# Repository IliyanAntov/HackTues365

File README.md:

# HackTues365 Project
Defuse the bomb.

## Game Rules And Tutorial

Work with a partner to defuse the bomb.
One of the two players should only look at the instructions while the other one is defusing the bomb.
Adhere to the time limit otherwise the bomb explodes.

Have fun!

## How do I play?

Connect your **Arduino** board the PC and then start the Generator app.
Click **Generate** and wait for the instructions to upload.
You can then disconnect the board and start playing the game.

## Used Technologies

All of the game logic relies on the **Arduino** to run on.
The random values for each game are generated by a **.NET Windows Forms Application**.
Both processes are connected via a serial connection based on the **System.IO.Ports** library included in **.NET**.

## Dependecies

The schematic is based on an open source Arduino Mega 2560 design by [Yoyodyne Monkey Works, Inc.](https://github.com/YoyodyneMonkeyWorks)

Repository [link](https://github.com/YoyodyneMonkeyWorks/KiCad/tree/master/Arduino_MEGA_2560-Rev3)

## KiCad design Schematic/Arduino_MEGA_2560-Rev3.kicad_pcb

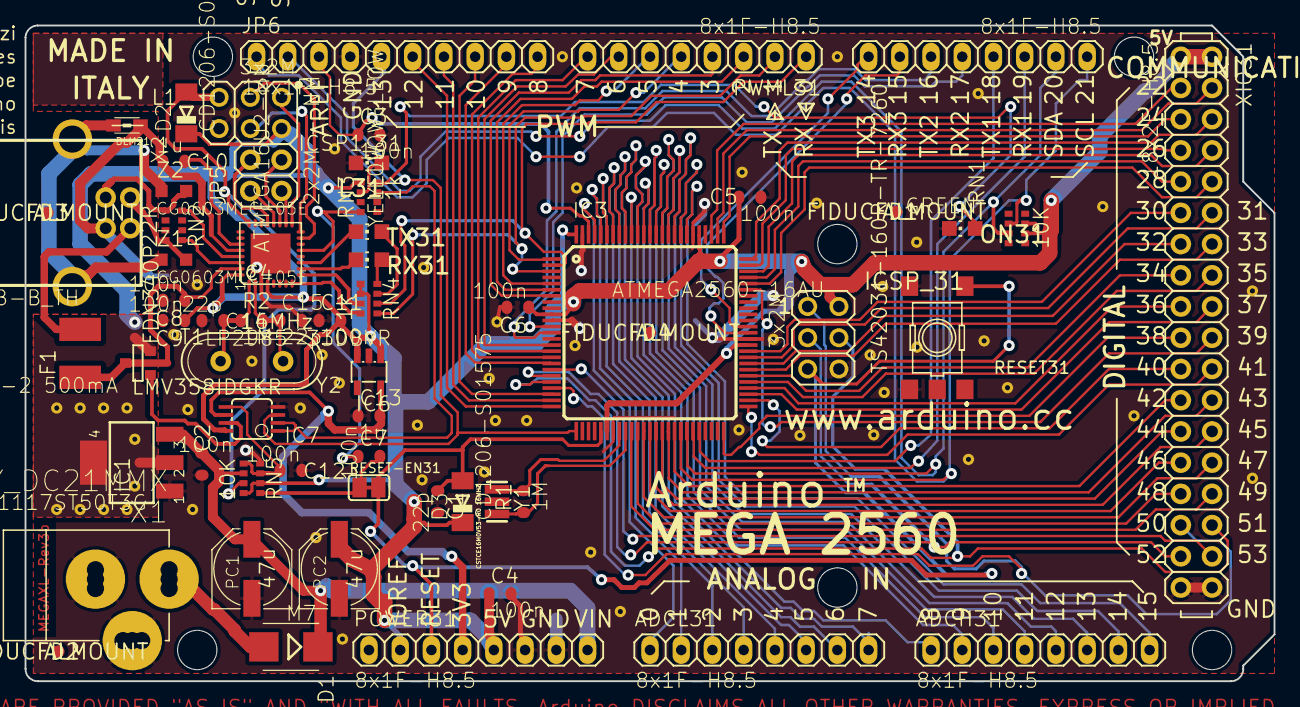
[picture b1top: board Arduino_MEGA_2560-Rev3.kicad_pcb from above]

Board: 2 copper layers, 101.6 x 53.3 mm, 69 parts (0 on the bottom side), 110 nets.

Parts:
@HOLE0, @HOLE1, @HOLE2, @HOLE3, @HOLE4, @HOLE5: (no value)
ADCH31: 8x1F-H8.5; 1X08
ADCL31: 8x1F-H8.5; 1X08
C1, C14, C15: 22p; C0603-ROUND
C2, C3, C4, C5, C6, C7, C8, C9, C11, C12: 100n; C0603-ROUND
C10, C13: 1u; C0603-ROUND
COMMUNICATION31: 8x1F-H8.5; 1X08
D1: M7; SMB
D2, D3: CD1206-S01575; MINIMELF
F1: MF-MSMF050-2 500mA; L1812
FD1, FD2, FD3, FD4: FIDUCIALMOUNT; FIDUCIA-MOUNT
GROUND31: SJ
IC1: NCP1117ST50T3G; SOT223
IC3: ATMEGA2560-16AU; TQFP100
IC4: ATMEGA16U2-MU; MLF32
IC6: LP2985-33DBVR; SOT23-DBV
IC7: LMV358IDGKR; MSOP08
ICSP1_31: 3x2M; 2X03
ICSP_31: 3x2M; 2X03
JP5: 2x2M - NM; 2X02
JP6: 10x1F-H8.5; 1X10
L1: BLM21; 0805
L31: YELLOW; CHIP-LED0805
ON31: GREEN; CHIP-LED0805
PC1, PC2: 47u; PANASONIC_D
POWER31: 8x1F-H8.5; 1X08
PWML31: 8x1F-H8.5; 1X08
R1, R2: 1M; R0603-ROUND
RESET31: TS42031-160R-TR-7260; TS42
RESET-EN31: SJ
RN1, RN5: 10K; CAT16
RN2: 22R; CAY16
RN3, RN4: 1k; CAY16
RX31: YELLOW; CHIP-LED0805
T1: FDN340P; SOT-23
TX31: YELLOW; CHIP-LED0805
U$1: DISCLAIMER
X1: POWERSUPPLY_DC21MMX; POWERSUPPLY_DC-21MM
X2: USB-B_TH; PN61729
XIO31: 18x2F-H8.5; 2X18
Y1: CSTCE16M0V53-R0 16MHZ; RESONATOR
Y2: 16MHz; QS
Z1, Z2: CG0603MLC-05E; CT%2fCN0603

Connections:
+3V3: C13.2, IC6.5, IC7.6, POWER31.4
+5V: C4.1, C5.1, C6.1, C9.1, C11.2, D2.C, D3.C, IC1.2, IC1.4, IC3.10, IC3.31, IC3.61, IC3.80, IC3.100, IC4.4, IC4.32, IC6.1, IC6.3, IC7.8, ICSP1_31.2, ICSP_31.2, PC2.+, POWER31.2, POWER31.5, RN1.6, RN1.7, RN3.1, RN4.5, RN4.6, RN5.2, RN5.8, T1.2, XIO31.1, XIO31.2
/8PB4: IC4.18, JP5.1
/8PB5: IC4.19, JP5.3
/8PB6: IC4.20, JP5.2
/8PB7: IC4.21, JP5.4
/ADC0: ADCL31.1, IC3.97
/ADC1: ADCL31.2, IC3.96
/ADC2: ADCL31.3, IC3.95
/ADC3: ADCL31.4, IC3.94
/ADC4: ADCL31.5, IC3.93
/ADC5: ADCL31.6, IC3.92
/ADC6: ADCL31.7, IC3.91
/ADC7: ADCL31.8, IC3.90
/ADC8: ADCH31.1, IC3.89
/ADC9: ADCH31.2, IC3.88
/ADC10: ADCH31.3, IC3.87
/ADC11: ADCH31.4, IC3.86
/ADC12: ADCH31.5, IC3.85
/ADC13: ADCH31.6, IC3.84
/ADC14: ADCH31.7, IC3.83
/ADC15: ADCH31.8, IC3.82
/AREF: C3.1, IC3.98, JP6.3
/CMP: C12.2, IC7.5, RN5.3, RN5.5
/D+: RN2.5, X2.3, Z2.2
/D-: RN2.8, X2.2, Z1.2
/DTR: C7.1, IC4.13, RN3.4
/GATE_CMD: IC7.7, T1.3
/L13: IC7.1, IC7.2, RN3.7
/M8RXD: IC4.9, RN4.7
/M8TXD: IC4.8, RN4.8
/MISO2: IC4.17, ICSP1_31.1
/MOSI2: IC4.16, ICSP1_31.4
/N$2: L31.A, RN3.2
/N$3: ON31.A, RN3.8
/N$54: RN4.4, RX31.A
/N$55: RN4.3, TX31.A
/PA0: IC3.78, XIO31.3
/PA1: IC3.77, XIO31.4
/PA2: IC3.76, XIO31.5
/PA3: IC3.75, XIO31.6
/PA4: IC3.74, XIO31.7
/PA5: IC3.73, XIO31.8
/PA6: IC3.72, XIO31.9
/PA7: IC3.71, XIO31.10
/PB0: IC3.19, XIO31.34
/PB1: IC3.20, ICSP_31.3, XIO31.33
/PB2: IC3.21, ICSP_31.4, XIO31.32
/PB3: IC3.22, ICSP_31.1, XIO31.31
/PB4: IC3.23, JP6.8
/PB5: IC3.24, JP6.7
/PB6: IC3.25, JP6.6
/PB7: IC3.26, IC7.3, JP6.5
/PC0: IC3.53, XIO31.18
/PC1: IC3.54, XIO31.17
/PC2: IC3.55, XIO31.16
/PC3: IC3.56, XIO31.15
/PC4: IC3.57, XIO31.14
/PC5: IC3.58, XIO31.13
/PC6: IC3.59, XIO31.12
/PC7: IC3.60, XIO31.11
/PD7: IC3.50, XIO31.19
/PE0: IC3.2, PWML31.1, RN4.2
/PE1: IC3.3, PWML31.2, RN4.1
/PE3: IC3.5, PWML31.6
/PE4: IC3.6, PWML31.3
/PE5: IC3.7, PWML31.4
/PG0: IC3.51, XIO31.22
/PG1: IC3.52, XIO31.21
/PG2: IC3.70, XIO31.20
/PG5: IC3.1, PWML31.5
/PH3: IC3.15, PWML31.7
/PH4: IC3.16, PWML31.8
/PH5: IC3.17, JP6.10
/PH6: IC3.18, JP6.9
/PL0: IC3.35, XIO31.30
/PL1: IC3.36, XIO31.29
/PL2: IC3.37, XIO31.28
/PL3: IC3.38, XIO31.27
/PL4: IC3.39, XIO31.26
/PL5: IC3.40, XIO31.25
/PL6: IC3.41, XIO31.24
/PL7: IC3.42, XIO31.23
/PWRIN: D1.A, X1.2
/RD+: IC4.29, RN2.4
/RD-: IC4.30, RN2.1
/RESET: C1.1, C7.2, D3.A, IC3.30, ICSP_31.5, POWER31.3, RESET31.3, RESET31.4, RESET-EN31.1, RESET-EN31.2, RN5.1
/RESET2: D2.A, IC4.24, ICSP1_31.5, RN5.7
/RXD1: COMMUNICATION31.3, IC3.45
/RXD2: COMMUNICATION31.5, IC3.12
/RXD3: COMMUNICATION31.7, IC3.63
/RXL: IC4.10, RX31.C
/SCK2: IC4.15, ICSP1_31.3
/SCL: COMMUNICATION31.1, IC3.43, JP6.1, RN1.2
/SDA: COMMUNICATION31.2, IC3.44, JP6.2, RN1.3
/TXD1: COMMUNICATION31.4, IC3.46
/TXD2: COMMUNICATION31.6, IC3.13
/TXD3: COMMUNICATION31.8, IC3.64
/TXL: IC4.11, TX31.C
/UGND: C10.2, GROUND31.1, IC4.28, L1.1, X2.4
/USBVCC: C8.1, F1.1, IC4.31, T1.1
/USHIELD: L1.2, X2.P$1, X2.P$2, Z1.1, Z2.1
/VIN: C2.1, D1.C, IC1.3, PC1.+, POWER31.8, RN5.6
/VUCAP: C10.1, IC4.27
/XT1: C14.1, IC4.1, R2.1, Y2.2
/XT2: C15.1, IC4.2, R2.2, Y2.1
/XTAL1: IC3.34, R1.1, Y1.3
/XTAL2: IC3.33, R1.2, Y1.1
/XVCC: F1.2, X2.1
GND: C1.2, C2.2, C3.2, C4.2, C5.2, C6.2, C8.2, C9.2, C11.1, C12.1, C13.1, C14.2, C15.2, GROUND31.2, IC1.1, IC3.11, IC3.32, IC3.62, IC3.81, IC3.99, IC4.3, IC4.33, IC6.2, IC7.4, ICSP1_31.6, ICSP_31.6, JP6.4, L31.C, ON31.C, PC1.-, PC2.-, POWER31.6, POWER31.7, RESET31.1, RESET31.2, RN3.5, RN5.4, X1.1, X1.3, XIO31.35, XIO31.36, Y1.2

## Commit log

2019-03-15 Added the js side of the communication
2019-03-15 Added some basic code for the button game
2019-03-15 Added the arduino side of the communication
2019-03-15 finished communication
2019-03-15 added custom usb port
2019-03-15 Fixed the button game
2019-03-15 Added button_game randomizer
2019-03-15 Added timer
2019-03-15 Made the basics of the morse code game
2019-03-15 Made it possible to have all characters in the alphabet usable in morse
2019-03-15 Fixed communication
2019-03-15 Fixed some things in the code
2019-03-15 Added a 7 segment indicator
2019-03-15 Made some fixes
2019-03-15 Sending info to Arduino with C#
2019-03-16 Adding Simon says game. Some fixes for morse code game..
2019-03-16 Shortened the code for the button game
2019-03-16 Fixed morse code game
2019-03-16 Renamed simon_says_game.ino
2019-03-16 Fixed random number generating issues
2019-03-16 Moved morse code game to the right place
2019-03-16 Moved Delay class in seperate file
2019-03-16 Formatting
2019-03-16 Added abstract class Game
2019-03-16 Added a ButtonGame class
2019-03-16 Fixed mixed files
2019-03-16 Made abstract class workgit add *git add *git add *
2019-03-16 Added Morse Code Game ranomization and output
2019-03-16 Implementing the most beautiful code ever
2019-03-16 Didn't fix anything ;(
2019-03-16 Fixed button game
2019-03-16 Removed some unnecessary files
2019-03-16 Fixed Morse Code Generation
2019-03-16 Renamed all the variables in ButtonGame
2019-03-16 renamed variables in morse code game
2019-03-16 Fixed Button game, Morse Code Game and Simon Says Game
2019-03-16 Morse Code Fully Randomized
2019-03-16 added 7 segment library
2019-03-16 Fixed the timer and added it into allGames.ino
2019-03-16 Finalized morse code game
2019-03-16 updated sevenSegment.h
2019-03-16 Fixed buttonGame
2019-03-16 Added morse code reference image and formatted text
2019-03-16 Fixed some things
2019-03-16 Fixed some bugs in the button game
2019-03-16 Font size and font family + column heads
2019-03-16 Restructurized most of the code
2019-03-16 Fixed simon says
2019-03-16 cleared some empty directories
2019-03-16 Restructurized Files
2019-03-16 Removed old unused javascript
2019-03-16 Made timer non-blocking
2019-03-16 last timer was wrong file
2019-03-16 Updated README.md file
2019-03-16 made button class seperate file
2019-03-16 fixed timer and renamed files
2019-03-16 fixed some things in the ButtonGame
2019-03-16 changed pins
2019-03-16 refactored some code
2019-03-16 Added schematic
2019-03-16 updated pins
2019-03-16 Added Button Game Schematic
2019-03-16 Added Simon Says Schematic
2019-03-16 Schematic Annotated
2019-03-16 Update README.md File
2019-03-16 starting work on connectin manual and bomb
2019-03-16 Fixed spelling
2019-03-16 bugs
2019-03-17 Schematic Edited
2019-03-17 Added Completion Indication to Schematic
2019-03-17 Schematic
2019-03-17 Win/Lose condition
2019-03-17 progress
2019-03-17 Added screenshots of the schematic
